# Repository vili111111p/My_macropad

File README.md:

# My_macropad
This is my macropad. I designt it for multiple usecases. With 9 buttons it can be used for a lot of things. And it also have 16 rgb leds, so it looks also great.

## CAD Model
It has 2 pieces, that connect together with screws and heatset inserts. the bottom piece should be from white filament, so it diffuses the filament.

All together

Case

## PCB
It is two sided. It has a bit tangled connections between the RP2040 and the components. I tried to make it the best i can.

Schematic

PCB

## Firmware
I made it in KMK (It was the easiest for me). The buttons are programmed to do a couple macros (Mute, undo, redo etc.).

## BOM
 - 8x Cherry MX Switches
 - 8x DSA Keycaps
 - 1x EC11 Rotary Encoder
 - 9x 1N4148 DO-35 Diodes
 - 1x 0.91" 128x32 OLED Display
 - 1x XIAO RP2040
 - 16x WS2812B LEDs
 - 1x case (2x 3d printed part)
 - 10x M3x5x4 Heatset inserts
 - 10x M3x12mm SHCS Bolts

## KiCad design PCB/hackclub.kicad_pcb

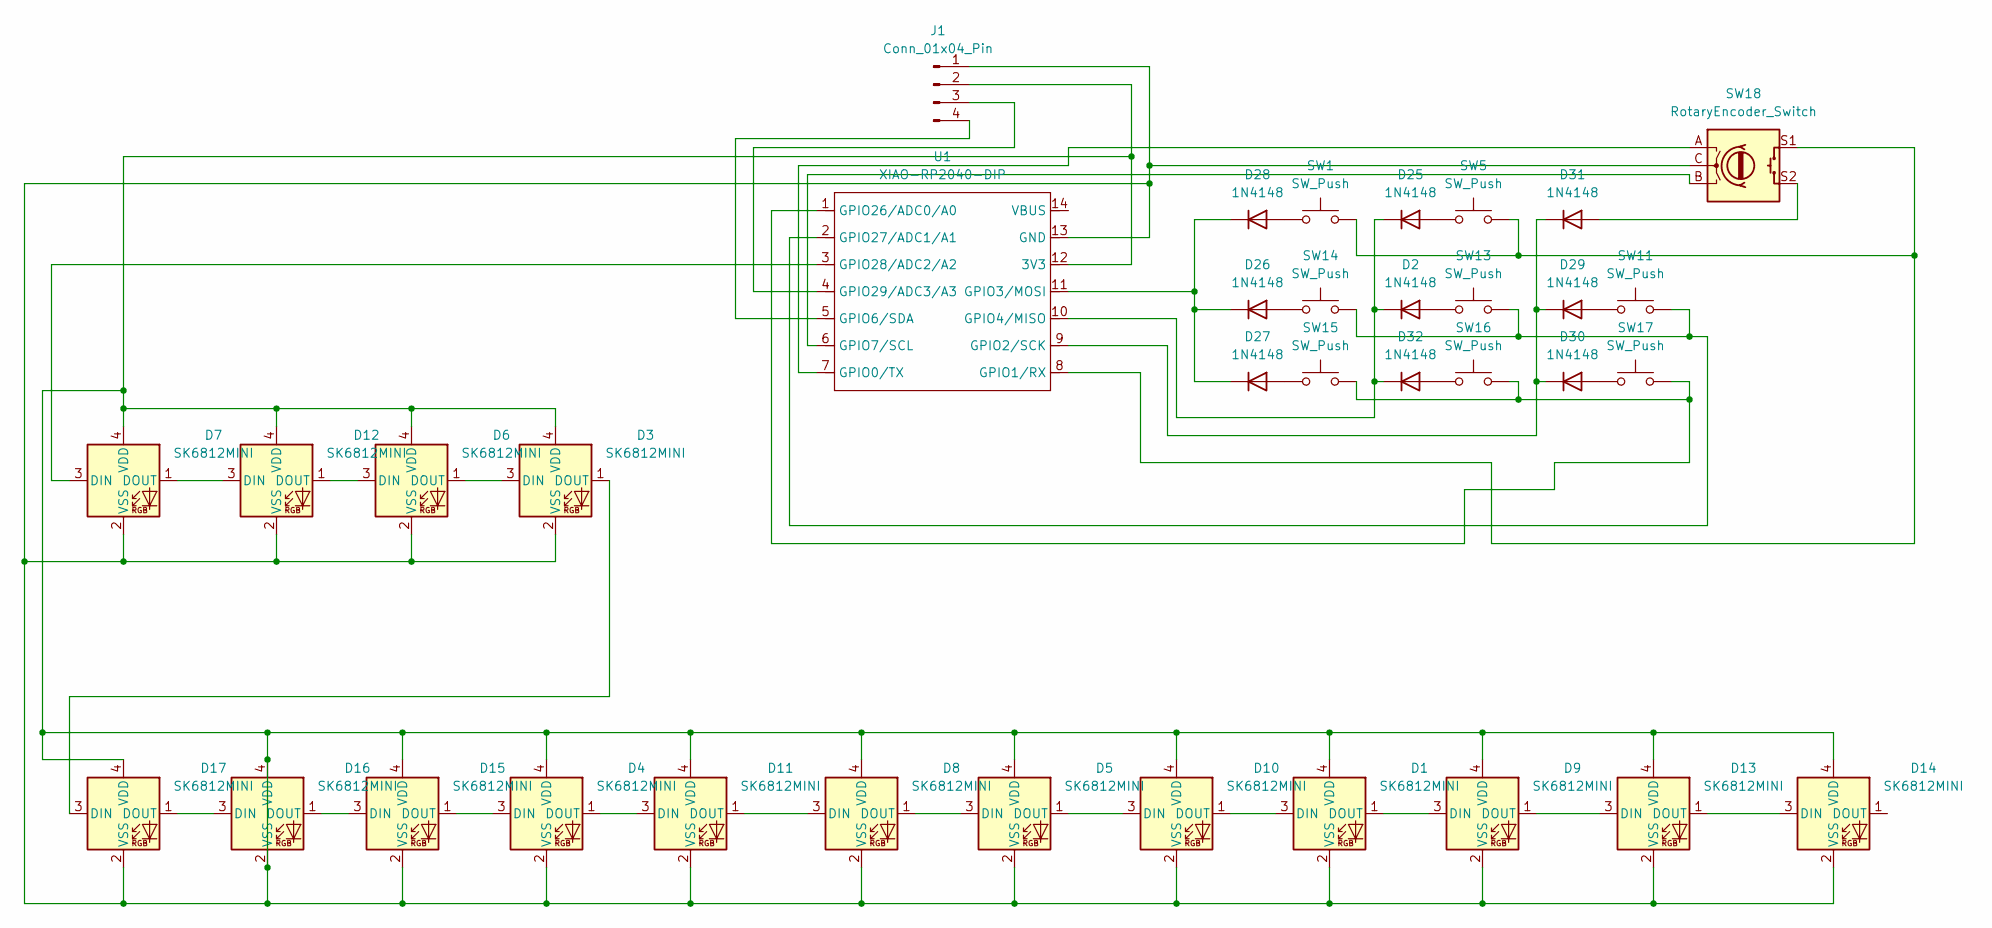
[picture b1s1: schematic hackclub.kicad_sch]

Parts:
D1, D3, D4, D5, D6, D7, D8, D9, D10, D11, D12, D13, D14, D15, D16, D17: SK6812MINI; LED_SK6812MINI_PLCC4_3.5x3.5mm_P1.75mm
D2, D25, D26, D27, D28, D29, D30, D31, D32: 1N4148; D_DO-35_SOD27_P7.62mm_Horizontal
J1: Conn_01x04_Pin; SSD1306-0.91-OLED-4pin-128x32
SW1, SW5, SW11, SW13, SW14, SW15, SW16, SW17: SW_Push; SW_Cherry_MX_1.00u_PCB
SW18: RotaryEncoder_Switch; RotaryEncoder_Alps_EC11E-Switch_Vertical_H20mm
U1: XIAO-RP2040-DIP

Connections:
unnamed: D1.3 (DIN), D10.1 (DOUT)
unnamed: D1.1 (DOUT), D9.3 (DIN)
unnamed: D1.2 (VSS), D1.4 (VDD), D3.2 (VSS), D3.4 (VDD), D4.2 (VSS), D4.4 (VDD), D5.2 (VSS), D5.4 (VDD), D6.2 (VSS), D6.4 (VDD), D7.2 (VSS), D7.4 (VDD), D8.2 (VSS), D8.4 (VDD), D9.2 (VSS), D9.4 (VDD), D10.2 (VSS), D10.4 (VDD), D11.2 (VSS), D11.4 (VDD), D12.2 (VSS), D12.4 (VDD), D13.2 (VSS), D13.4 (VDD), D14.2 (VSS), D14.4 (VDD), D15.2 (VSS), D15.4 (VDD), D16.2 (VSS), D16.4 (VDD), D17.2 (VSS), D17.4 (VDD), J1.1, J1.2, SW18.C, U1.12 (3V3), U1.13 (GND)
unnamed: D2.2 (A), SW13.1
unnamed: D2.1 (K), D25.1 (K), D32.1 (K), U1.10 (GPIO4/MISO)
unnamed: D3.3 (DIN), D6.1 (DOUT)
unnamed: D5.3 (DIN), D8.1 (DOUT)
unnamed: D7.3 (DIN), U1.3 (GPIO28/ADC2/A2)
unnamed: D5.1 (DOUT), D10.3 (DIN)
unnamed: D4.1 (DOUT), D11.3 (DIN)
unnamed: D8.3 (DIN), D11.1 (DOUT)
unnamed: D7.1 (DOUT), D12.3 (DIN)
unnamed: D6.3 (DIN), D12.1 (DOUT)
unnamed: D9.1 (DOUT), D13.3 (DIN)
unnamed: D13.1 (DOUT), D14.3 (DIN)
unnamed: D15.3 (DIN), D16.1 (DOUT)
unnamed: D4.3 (DIN), D15.1 (DOUT)
unnamed: D16.3 (DIN), D17.1 (DOUT)
unnamed: D3.1 (DOUT), D17.3 (DIN)
unnamed: D25.2 (A), SW5.1
unnamed: D26.2 (A), SW14.1
unnamed: D26.1 (K), D27.1 (K), D28.1 (K), U1.11 (GPIO3/MOSI)
unnamed: D27.2 (A), SW15.1
unnamed: D28.2 (A), SW1.1
unnamed: D29.2 (A), SW11.1
unnamed: D29.1 (K), D30.1 (K), D31.1 (K), U1.9 (GPIO2/SCK)
unnamed: D30.2 (A), SW17.1
unnamed: D31.2 (A), SW18.S2
unnamed: D32.2 (A), SW16.1
unnamed: J1.3, U1.4 (GPIO29/ADC3/A3)
unnamed: J1.4, U1.5 (GPIO6/SDA)
unnamed: SW18.A, U1.7 (GPIO0/TX)
unnamed: SW1.2, SW5.2, SW18.S1, U1.8 (GPIO1/RX)
unnamed: SW18.B, U1.6 (GPIO7/SCL)
unnamed: SW15.2, SW16.2, SW17.2, U1.1 (GPIO26/ADC0/A0)
unnamed: SW11.2, SW13.2, SW14.2, U1.2 (GPIO27/ADC1/A1)

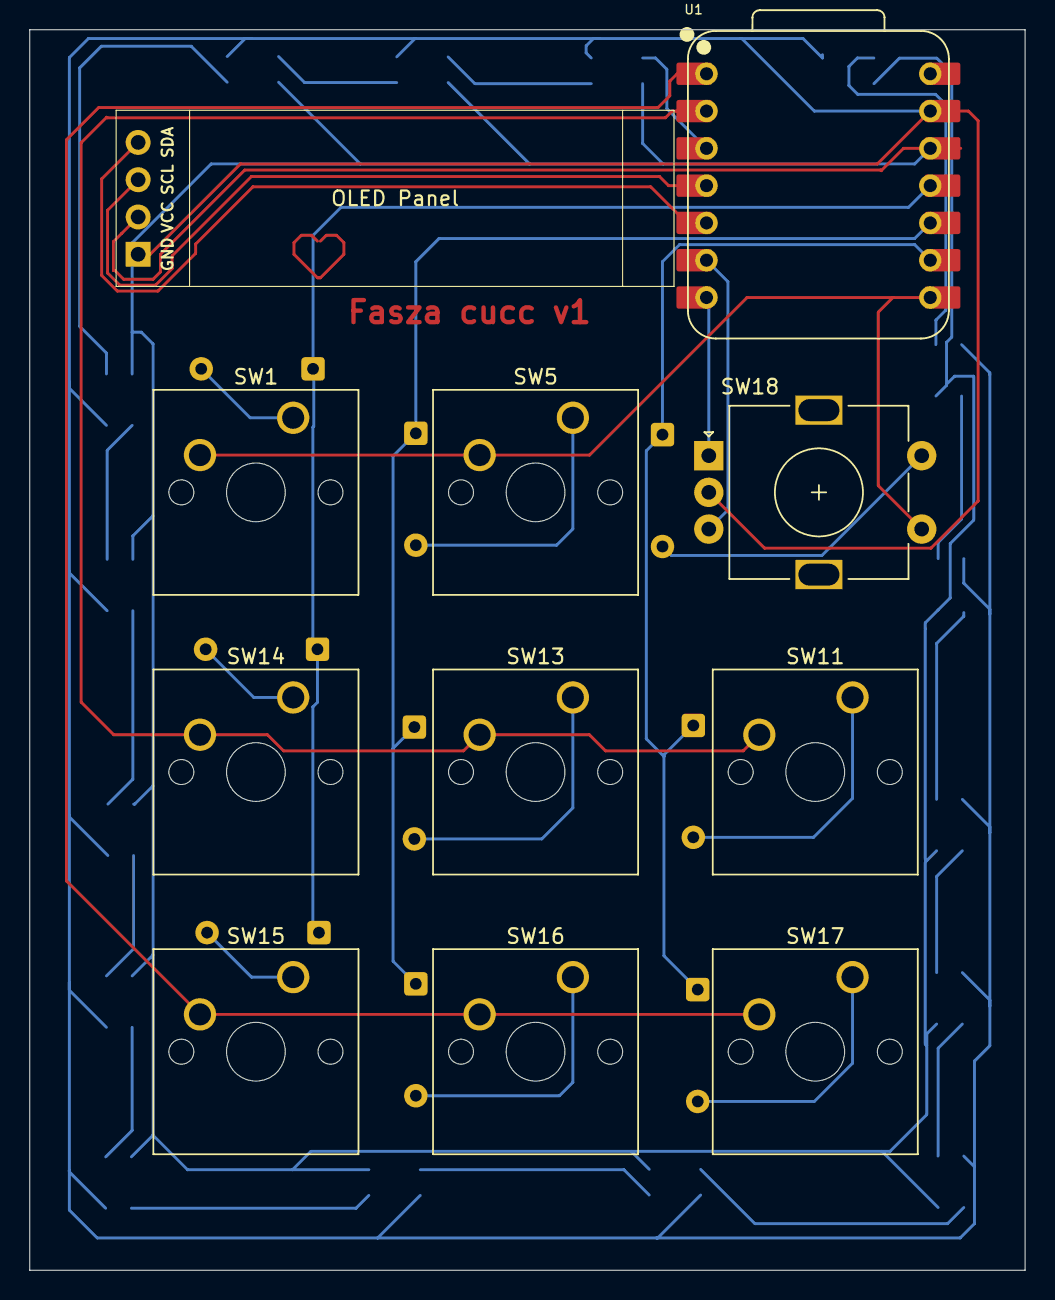
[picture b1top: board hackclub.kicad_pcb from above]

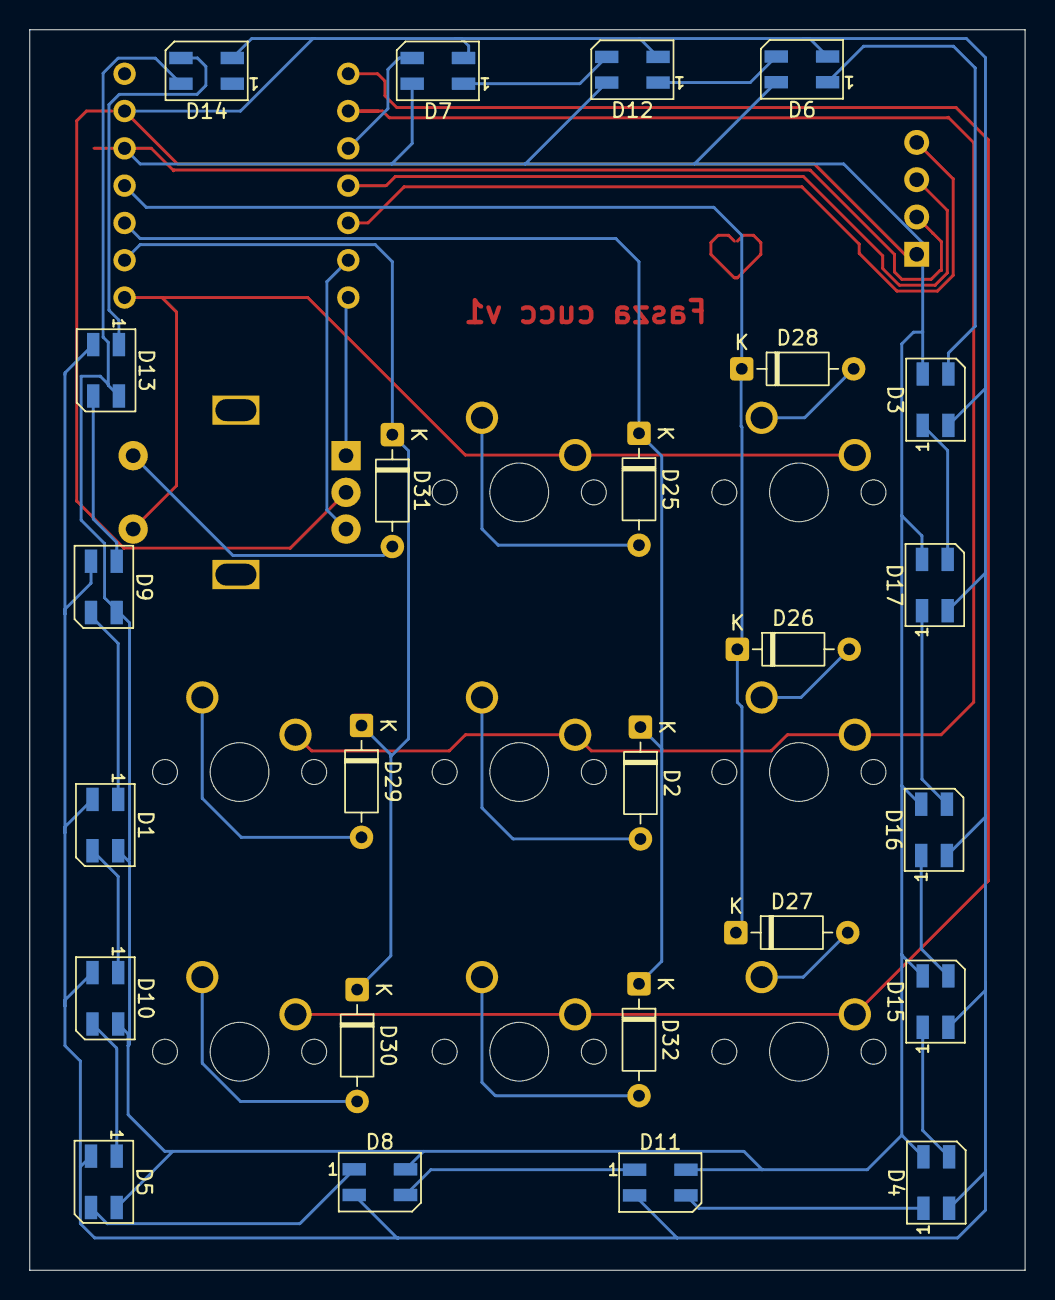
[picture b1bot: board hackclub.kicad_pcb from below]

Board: 2 copper layers, 67.8 x 84.5 mm, 36 parts (25 on the bottom side), 36 nets.

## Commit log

2025-12-02 Add initial content to readme.md
